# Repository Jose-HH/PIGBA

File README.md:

# PIGBA

## Introduction

PIGBA is a RPi Zero based retro emulation portable console

## WIP

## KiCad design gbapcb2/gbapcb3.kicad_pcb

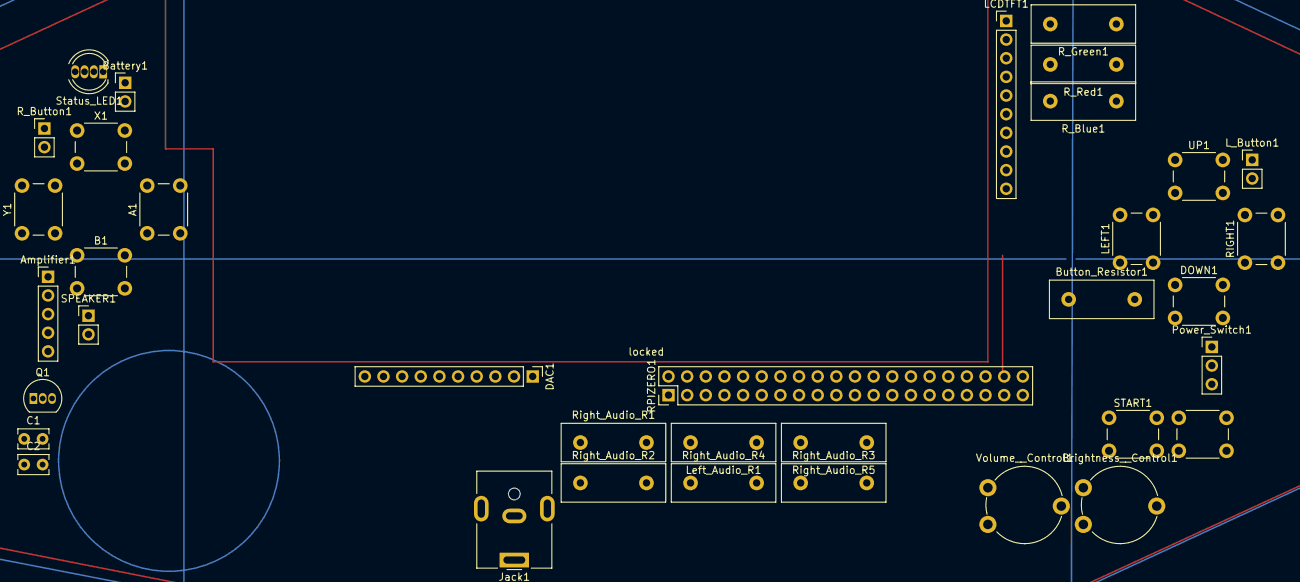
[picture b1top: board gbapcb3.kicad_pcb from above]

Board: 2 copper layers, 36 parts (0 on the bottom side), 47 nets.

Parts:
A1: SW_Push_Dual; SW_PUSH_6mm
Amplifier1: Conn_01x05; PinHeader_1x05_P2.54mm_Vertical
B1: SW_Push_Dual; SW_PUSH_6mm
Battery1: Conn_01x02; PinHeader_1x02_P2.54mm_Vertical
Brightness__Control1: 10k; Potentiometer_Piher_PT-10-V10_Vertical
Button_Resistor1: 10k; R_Box_L14.0mm_W5.0mm_P9.00mm
C1, C2: C_Polarized_Small; C_Rect_L4.0mm_W2.5mm_P2.50mm
DAC1: Conn_01x10; PinHeader_1x10_P2.54mm_Vertical
DOWN1: SW_Push_Dual; SW_PUSH_6mm
Jack1: AudioJack3; BarrelJack_CUI_PJ-063AH_Horizontal
LCDTFT1: Conn_01x10; PinHeader_1x10_P2.54mm_Vertical
LEFT1: SW_Push_Dual; SW_PUSH_6mm
L_Button1: Conn_01x02; PinHeader_1x02_P2.54mm_Vertical
Left_Audio_R1: 100; R_Box_L14.0mm_W5.0mm_P9.00mm
Power_Switch1: SW_SPDT; PinHeader_1x03_P2.54mm_Vertical
Q1: S8050; TO-92_Inline
RIGHT1: SW_Push_Dual; SW_PUSH_6mm
RPIZERO1: Conn_02x20_Odd_Even; PinHeader_2x20_P2.54mm_Vertical
R_Blue1: 220; R_Box_L14.0mm_W5.0mm_P9.00mm
R_Button1: Conn_01x02; PinHeader_1x02_P2.54mm_Vertical
R_Green1: 220; R_Box_L14.0mm_W5.0mm_P9.00mm
R_Red1: 220; R_Box_L14.0mm_W5.0mm_P9.00mm
Right_Audio_R1, Right_Audio_R4: 100; R_Box_L14.0mm_W5.0mm_P9.00mm
Right_Audio_R2: 3220; R_Box_L14.0mm_W5.0mm_P9.00mm
Right_Audio_R3: 1000; R_Box_L14.0mm_W5.0mm_P9.00mm
Right_Audio_R5: 20; R_Box_L14.0mm_W5.0mm_P9.00mm
SPEAKER1: Conn_01x02; PinHeader_1x02_P2.54mm_Vertical
START1: SW_Push_Dual; SW_PUSH_6mm
Status_LED1: LED_RGBK; LED_D5.0mm-4_RGB
UP1: SW_Push_Dual; SW_PUSH_6mm
Volume__Control1: 10k; Potentiometer_Piher_PT-10-V10_Vertical
X1: SW_Push_Dual; SW_PUSH_6mm
Y1: SW_Push_Dual; SW_PUSH_6mm
locked: SW_Push_Dual; SW_PUSH_6mm

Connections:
unnamed: A1.1, RPIZERO1.32
unnamed: A1.2, B1.2, Button_Resistor1.2, DOWN1.1, LEFT1.1, L_Button1.2, RIGHT1.1, R_Button1.2, START1.1, UP1.1, X1.2, Y1.2, locked.1
unnamed: Amplifier1.1, C1.2, Left_Audio_R1.2, Right_Audio_R1.2
unnamed: Amplifier1.2, Amplifier1.5, DAC1.8, RPIZERO1.34, Right_Audio_R3.2, Right_Audio_R5.2, SPEAKER1.2, Volume__Control1.3
unnamed: Amplifier1.4, Brightness__Control1.1, DAC1.1, LCDTFT1.10, RPIZERO1.4, Right_Audio_R2.1, Right_Audio_R4.1
unnamed: B1.1, RPIZERO1.15
unnamed: Battery1.1, Power_Switch1.1 (A)
unnamed: Battery1.2, RPIZERO1.14
unnamed: Brightness__Control1.2, LCDTFT1.3
unnamed: Brightness__Control1.3, RPIZERO1.25
unnamed: Button_Resistor1.1, RPIZERO1.39
unnamed: C1.1, Q1.2 (B), Right_Audio_R2.2, Right_Audio_R3.1
unnamed: C2.1, Volume__Control1.1
unnamed: C2.2, Q1.3 (C), Right_Audio_R4.2
unnamed: DAC1.3, RPIZERO1.6
unnamed: DAC1.4, RPIZERO1.35
unnamed: DAC1.5, RPIZERO1.40
unnamed: DAC1.6, RPIZERO1.12
unnamed: DAC1.7, Left_Audio_R1.1
unnamed: DAC1.9, Right_Audio_R1.1
unnamed: DOWN1.2, RPIZERO1.31
unnamed: LCDTFT1.2, RPIZERO1.21
unnamed: LCDTFT1.4, RPIZERO1.23
unnamed: LCDTFT1.5, RPIZERO1.19
unnamed: LCDTFT1.6, RPIZERO1.18
unnamed: LCDTFT1.7, RPIZERO1.22
unnamed: LCDTFT1.8, RPIZERO1.24
unnamed: LCDTFT1.9, RPIZERO1.20
unnamed: LEFT1.2, RPIZERO1.33
unnamed: L_Button1.1, RPIZERO1.7
unnamed: Power_Switch1.2 (B), RPIZERO1.2
unnamed: Q1.1 (E), Right_Audio_R5.1
unnamed: RIGHT1.2, RPIZERO1.37
unnamed: RPIZERO1.10, R_Button1.1
unnamed: RPIZERO1.11, Y1.1
unnamed: RPIZERO1.13, X1.1
unnamed: RPIZERO1.26, R_Red1.2
unnamed: RPIZERO1.27, R_Blue1.2
unnamed: RPIZERO1.28, R_Green1.2
unnamed: RPIZERO1.29, UP1.2
unnamed: RPIZERO1.36, locked.2
unnamed: RPIZERO1.38, START1.2
unnamed: SPEAKER1.1, Volume__Control1.2
unnamed: R_Red1.1, Status_LED1.1 (RA)
unnamed: R_Green1.1, Status_LED1.2 (GA)
unnamed: R_Blue1.1, Status_LED1.3 (BA)
unnamed: RPIZERO1.30, Status_LED1.4 (K)
